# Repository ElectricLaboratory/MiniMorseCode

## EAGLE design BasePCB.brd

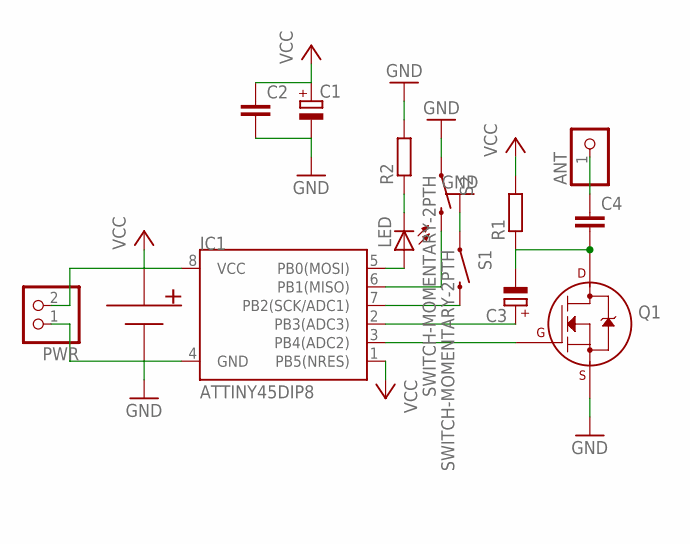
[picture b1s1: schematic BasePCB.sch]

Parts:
ANT: PINHD-1X1; 1X01
C1: CPOL-EUE2.5-6; E2,5-6
C2, C4: C-EU025-025X050; C025-025X050
C3: CPOL-EUE1.8-4; E1,8-4
IC1: ATTINY45DIP8; DIP08
LED: LED3MM
PWR: PINHD-1X2; 1X02
Q1: 2N7000_TO92; TO-92
R1, R2: R-EU_0207/7; 0207/7
S1, S2: SWITCH-MOMENTARY-2PTH; TACTILE-PTH
U$2: BATTERY-20MM

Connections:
ANT: ANT.1, C4.1
GND: C1.-, C2.2, IC1.4 (GND), PWR.1, Q1.1 (S), R2.2, S1.1, S2.1, U$2.- (NEG)
unnamed: IC1.3 (PB4(ADC2)), Q1.2 (G)
unnamed: C3.+, IC1.2 (PB3(ADC3))
unnamed: C3.-, C4.2, Q1.3 (D), R1.1
unnamed: LED.K (C), R2.1
unnamed: IC1.5 (PB0(MOSI)), LED.A
unnamed: IC1.6 (PB1(MISO)), S2.3 (2)
unnamed: IC1.7 (PB2(SCK/ADC1)), S1.3 (2)
VCC: C1.+, C2.1, IC1.1 (PB5(NRES)), IC1.8 (VCC), PWR.2, R1.2, U$2.+ (POS)

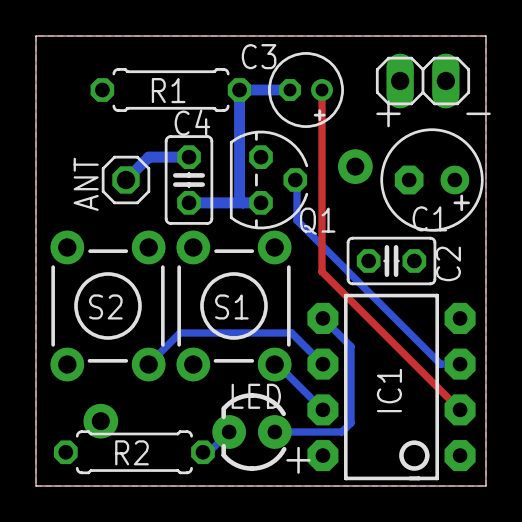
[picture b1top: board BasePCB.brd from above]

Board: 2 copper layers, 25.0 x 25.0 mm, 14 parts (1 on the bottom side), 10 nets.

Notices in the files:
parts and their libraries:
SparkFun-DigitalIC: Licensing: CC v3.0 Share-Alike You are welcome to use this library for commercial purposes.
